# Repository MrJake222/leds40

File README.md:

# LED4.0
4th edition of LED controls. ESP/WiFi based.

## Contents
* `3d` -- Enclosure,
* `board` -- PCB project,
* `board_jlc` -- 2 layer PCB project, with better attention to silk-screen,
* `esp8266` -- embedded code (platformio),
* `web` -- old-school PHP web app aggregating module controls,
* `leds41.txt` -- notes for future versions.

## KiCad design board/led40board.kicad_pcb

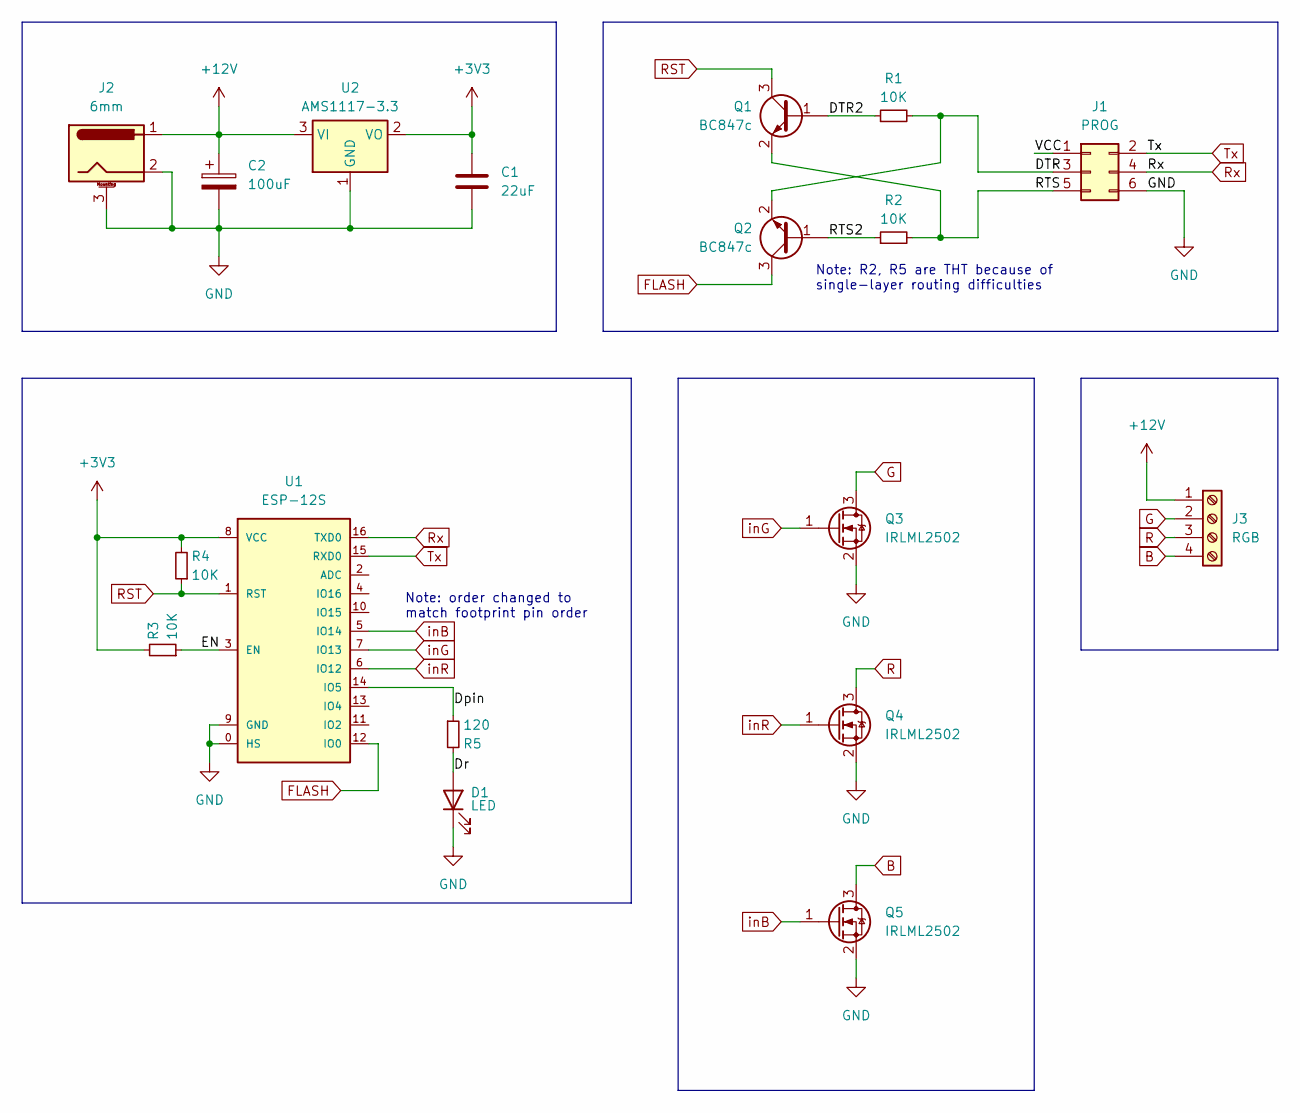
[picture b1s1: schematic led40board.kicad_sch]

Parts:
C1: 22uF; C_0805_2012Metric_Pad1.18x1.45mm_HandSolder
C2: 100uF; CP_Radial_D6.3mm_P2.50mm
D1: LED; LED_D3.0mm
J1: PROG; PinHeader_2x03_P2.54mm_Vertical
J2: 6mm; BarrelJack_CUI_PJ-102AH_Horizontal
J3: RGB; ARK_ScrewTerminal_5.00mm_4
Q1, Q2: BC847c; SOT-23_Handsoldering
Q3, Q4, Q5: IRLML2502; SOT-23_Handsoldering
R1, R3, R4: 10K; R_0603_1608Metric_Pad0.98x0.95mm_HandSolder
R2: 10K; R_Axial_DIN0204_L3.6mm_D1.6mm_P7.62mm_Horizontal
R5: 120; R_Axial_DIN0204_L3.6mm_D1.6mm_P7.62mm_Horizontal
U1: ESP-12S; esp
U2: AMS1117-3.3; SOT-223-3_TabPin2

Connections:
+3V3: C1.1, R3.2, R4.2, U1.8 (VCC), U2.2 (VO)
+12V: C2.1, J2.1, J3.1, U2.3 (VI)
/DTR: J1.3, Q2.2 (E), R1.2
/DTR2: Q1.1 (B), R1.1
/Dpin: R5.1, U1.14 (IO5)
/Dr: D1.2 (A), R5.2
/EN: R3.1, U1.3 (EN)
/RTS: J1.5, Q1.2 (E), R2.2
/RTS2: Q2.1 (B), R2.1
/VCC: J1.1
B: J3.4, Q5.3 (D)
FLASH: Q2.3 (C), U1.12 (IO0)
G: J3.2, Q3.3 (D)
GND: C1.2, C2.2, D1.1 (K), J1.6, J2.2, J2.3 (MountPin), Q3.2 (S), Q4.2 (S), Q5.2 (S), U1.0 (HS), U1.9 (GND), U2.1 (GND)
R: J3.3, Q4.3 (D)
RST: Q1.3 (C), R4.1, U1.1 (RST)
Rx: J1.4, U1.16 (TXD0)
Tx: J1.2, U1.15 (RXD0)
inB: Q5.1 (G), U1.5 (IO14)
inG: Q3.1 (G), U1.7 (IO13)
inR: Q4.1 (G), U1.6 (IO12)

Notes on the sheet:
Note: R2, R5 are THT because of single-layer routing difficulties
Note: order changed to match footprint pin order

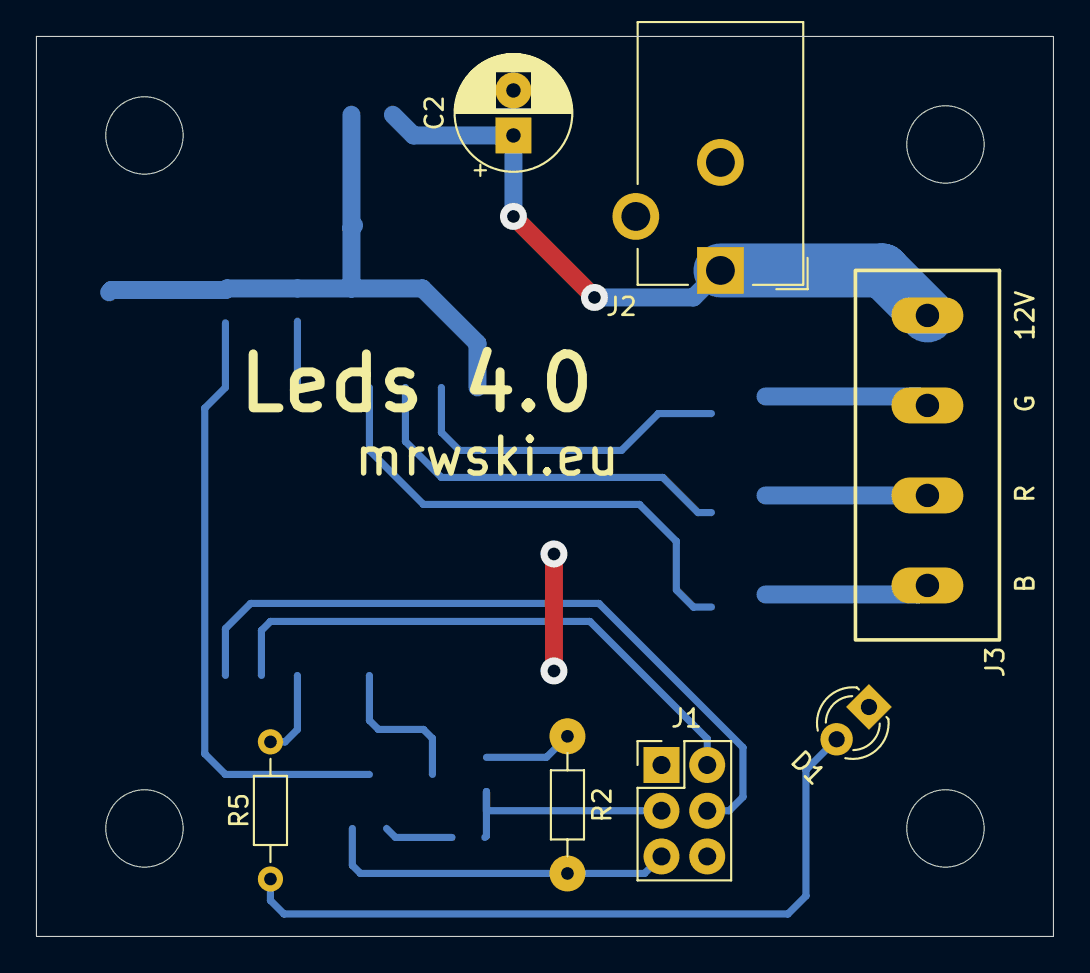
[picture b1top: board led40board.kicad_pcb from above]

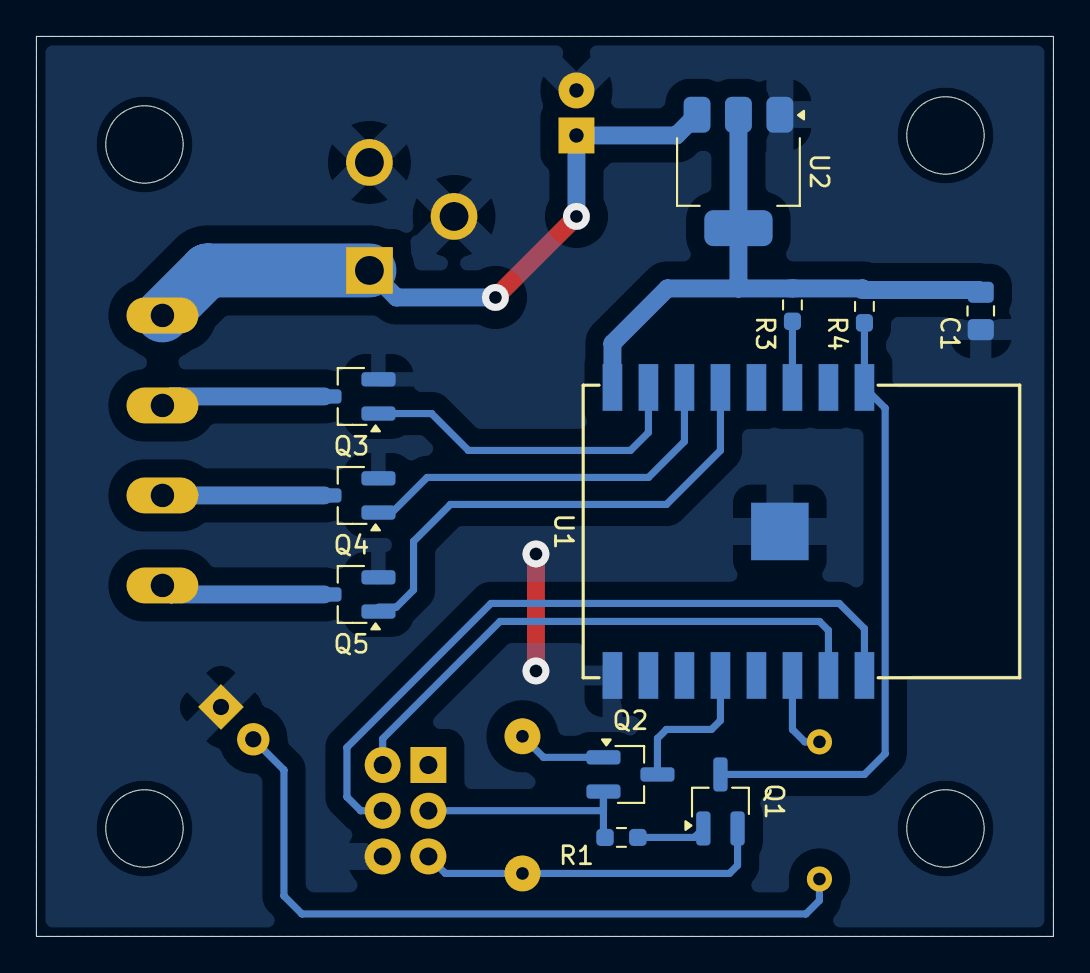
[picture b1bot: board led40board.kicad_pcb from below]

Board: 2 copper layers, 56.5 x 50.0 mm, 22 parts (11 on the bottom side), 20 nets.

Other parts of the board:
MNT: 4.3mm; MountingHole_4.3mm_M4
MNT#2, MNT#3, MNT#4: 4.3mm; MountingHole_4.3mm_M4

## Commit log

2024-08-18 Init, hw test
2024-08-18 WiFi config server ported from <piec>
2024-08-20 control led, power saving light sleep
2024-09-15 FTP server, name setting
2024-09-15 Led routes & simple web interface
2024-09-22 Fixes
    MAC address display in status
    better styling
    correct name fetching
2024-10-10 monorepo part 1
2024-10-10 added 3d files
2024-10-10 added boards
2024-10-10 added web & todo
2024-12-26 added web & todo
    added README.md
2024-12-26 Docker/compose env
2024-12-29 Room-based design
2024-12-29 Folder reorg and clean-ups
    Changed single to double quotes
2024-12-29 Quick slider fix
